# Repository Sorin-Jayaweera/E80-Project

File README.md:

# E80

This repository includes Arduino sketches (.ino) for the Teensy on the E80 motherboard.
The files for each lab are included in a separate folder.
The .ino files in each lab folder share the same name as the folder (e.g., `E80_Lab_01.ino` is in a folder named `E80_Lab_01.ino`).
This is a requirement for the Arduino IDE.

This respository also includes a [folder](./libraries/) of all the libraries you need for the various hardware peripherals on your motherboard (e.g., the GPS, and intertial measurement unit (IMU)).

The [MATLAB](./MATLAB/) folder contains the various MATLAB `.m` files which are used throughout the labs.

# How to Use this Repository
## Arduino IDE Setup
Follow the instructions below to download and use this code within the Arduino IDE.
1. If you have not yet installed the Arduino IDE, install it from [here](https://www.arduino.cc/en/software). The most version as of this writing is 2.0.3 but higher version numbers should also work fine.
2. Follow the instructions [here](https://www.pjrc.com/arduino-ide-2-0-0-teensy-support/) to configure support for the Teensy board within the Arduino IDE.

## Git Setup
Next you need to configure Git on your machine.
Git is a distributed version control system.
This means you can download a local clone of a collection of source code files and easily track the changes that you make to your code.
While we won't be using all the features of git in E80, we will introduce you to the main features that will enable you to interact with the code base for your robot.

First, you need to install Git on your computer.
We recommend that for this class you use [Git Desktop](https://desktop.github.com) which provides a convenient GUI interface for interacting with the code.

1. Download and install the latest version of Git Desktop [here](https://desktop.github.com).
2. Navigate to the [E80 Github repository](https://github.com/HMC-E80/E80) and click `Code > Open with GitHub Desktop`. You will get a prompt to download the repo and Github Desktop will ask you where to save the files. Choose a location on your hard drive where you want to save the files. You should choose a location on your hard drive (e.g., NOT in a folder which is synchronized in the cloud like a Google Drive File Stream folder) to minimize the chances of having any data corrupted. 
   - NOTE: If for some reason clicking `Open with GitHub Desktop` is not working properly, simply copy the URL for the repository (e.g., `https://github.com/HMC-E80/E80`) and then manually clone the repository in GitHub Desktop using `File > Clone Repository`. Enter the copied URL into the "Respository URL" field.

1. After downloading the code, open the Arduino IDE and open the Settings. Change the Sketchbook location to point to the folder you just downloaded. Restart the Arduino IDE. Now you if you click on the Sketchbook icon in the toolbar on the left side of the Arduino IDE you should see all the code for your E80 motherboard listed and available. Open up the `E80_Lab_01.ino` sketch and Verify it to check that it compiles and all the libraries are properly downloaded.

Congratulations, you are now set up and have the default E80 source code downloaded!
If you have any issues with these instructions, please reach out to one of the instructors.

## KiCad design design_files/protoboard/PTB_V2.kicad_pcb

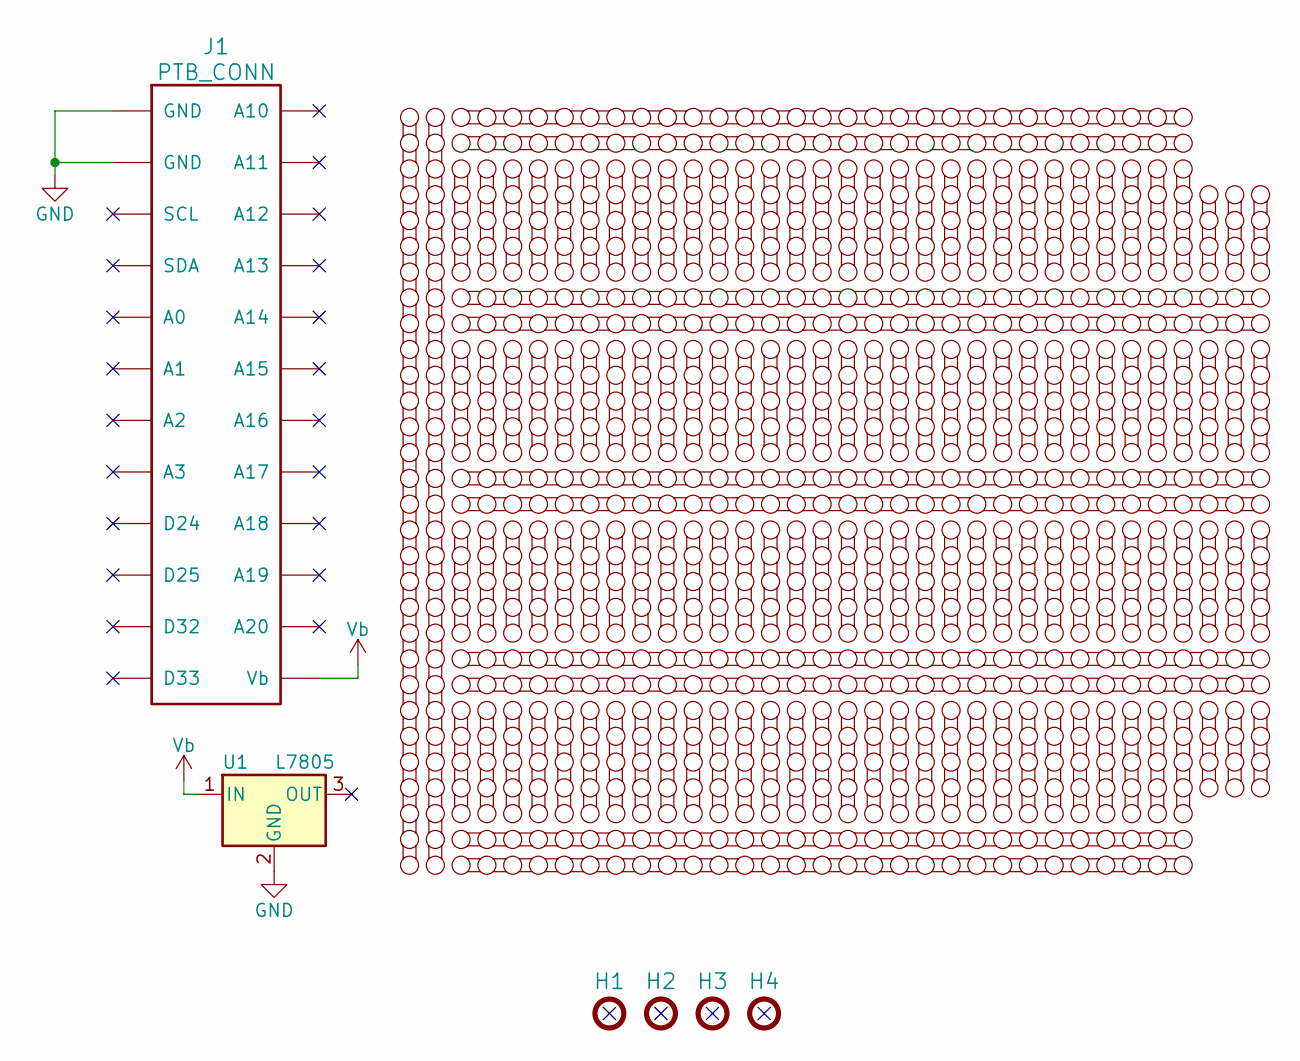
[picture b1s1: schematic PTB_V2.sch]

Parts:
H1, H2, H3, H4: MOUNTING_HOLE; Mounting_Hole
J1: PTB_CONN
U1: L7805; VREG
U2, U3: Row_30; Pad_30
U4, U5, U140, U141: Row_29; Pad_29
U6, U7, U8, U9, U10, U11, U12, U13, U14, U15, U16, U17, U18, U19, U20, U21, U22, U23, U24, U25, U26, U27, U28, U29, U30, U31, U32, U33, U34, U40, U41, U42, U43, U44, U45, U46, U47, U48, U49, U50, U51, U52, U53, U54, U55, U56, U57, U58, U59, U60, U61, U62, U63, U64, U65, U66, U67, U68, U69, U70, U71, U74, U75, U76, U77, U78, U79, U80, U81, U82, U83, U84, U85, U86, U87, U88, U89, U90, U91, U92, U93, U94, U95, U96, U97, U98, U99, U100, U101, U102, U103, U104, U105, U108, U109, U110, U111, U112, U113, U114, U115, U116, U117, U118, U119, U120, U121, U122, U123, U124, U125, U126, U127, U128, U129, U130, U131, U132, U133, U134, U135, U136: Row_5; Pad_5
U35, U36, U37, U137, U138, U139: Row_4; Pad_4
U38, U39, U72, U73, U106, U107: Row_32; Pad_32

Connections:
GND: J1.1 (GND), J1.2 (GND), U1.2 (GND)
Vb: J1.13 (Vb), U1.1 (IN)

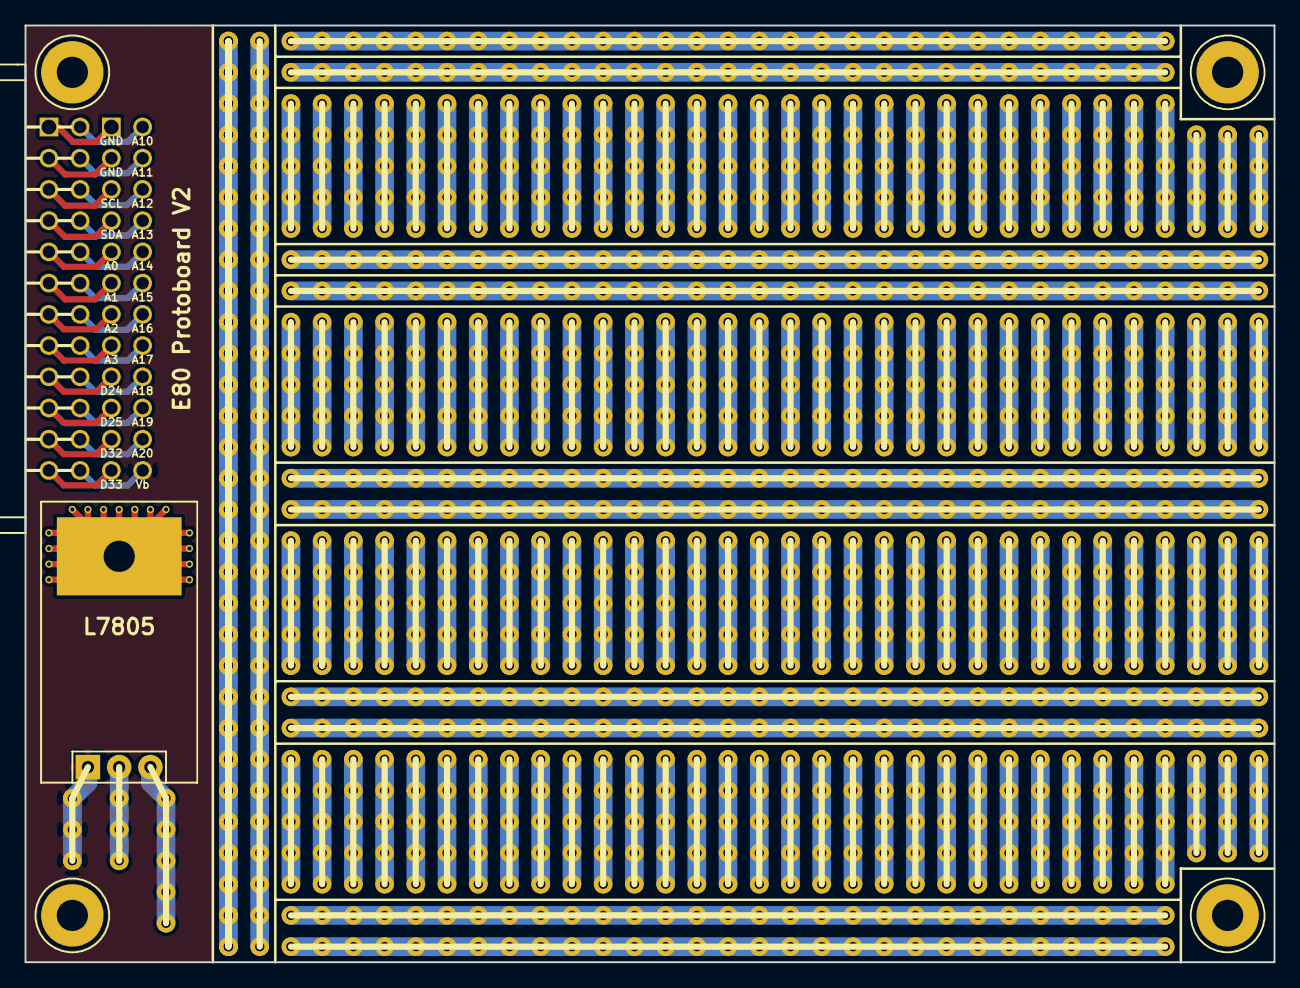
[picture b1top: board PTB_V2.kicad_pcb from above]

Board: 2 copper layers, 101.6 x 76.2 mm, 147 parts (0 on the bottom side), 2 nets.

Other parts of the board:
U3#2: Row_30; Pad_30

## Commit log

2025-03-24 Initialization
2025-03-24 Initialization
    Added the premade E80 code
2025-03-24 Updated hmc e80 stuff
2025-03-24 Create DepthControl.cpp
    Depth Control
2025-03-26 fixed the merge haha
    oops
2025-04-02 updated stuff, added v1 in sensor reading
2025-04-03 updated read sensors, added tds library
2025-04-03 updated readsensors
2025-04-14 Updated read all sensors
2025-04-15 added printing to dive
2025-04-17 working code!
2025-04-18 updated UV to not burn the motors
2025-04-25 automatic file incriments
2025-04-25 fixed depth
    also fixed adc logging
2025-04-26 real dana point!
2025-05-03 a ton of plots
2025-05-04 more plotting!
2025-05-05 added stats
